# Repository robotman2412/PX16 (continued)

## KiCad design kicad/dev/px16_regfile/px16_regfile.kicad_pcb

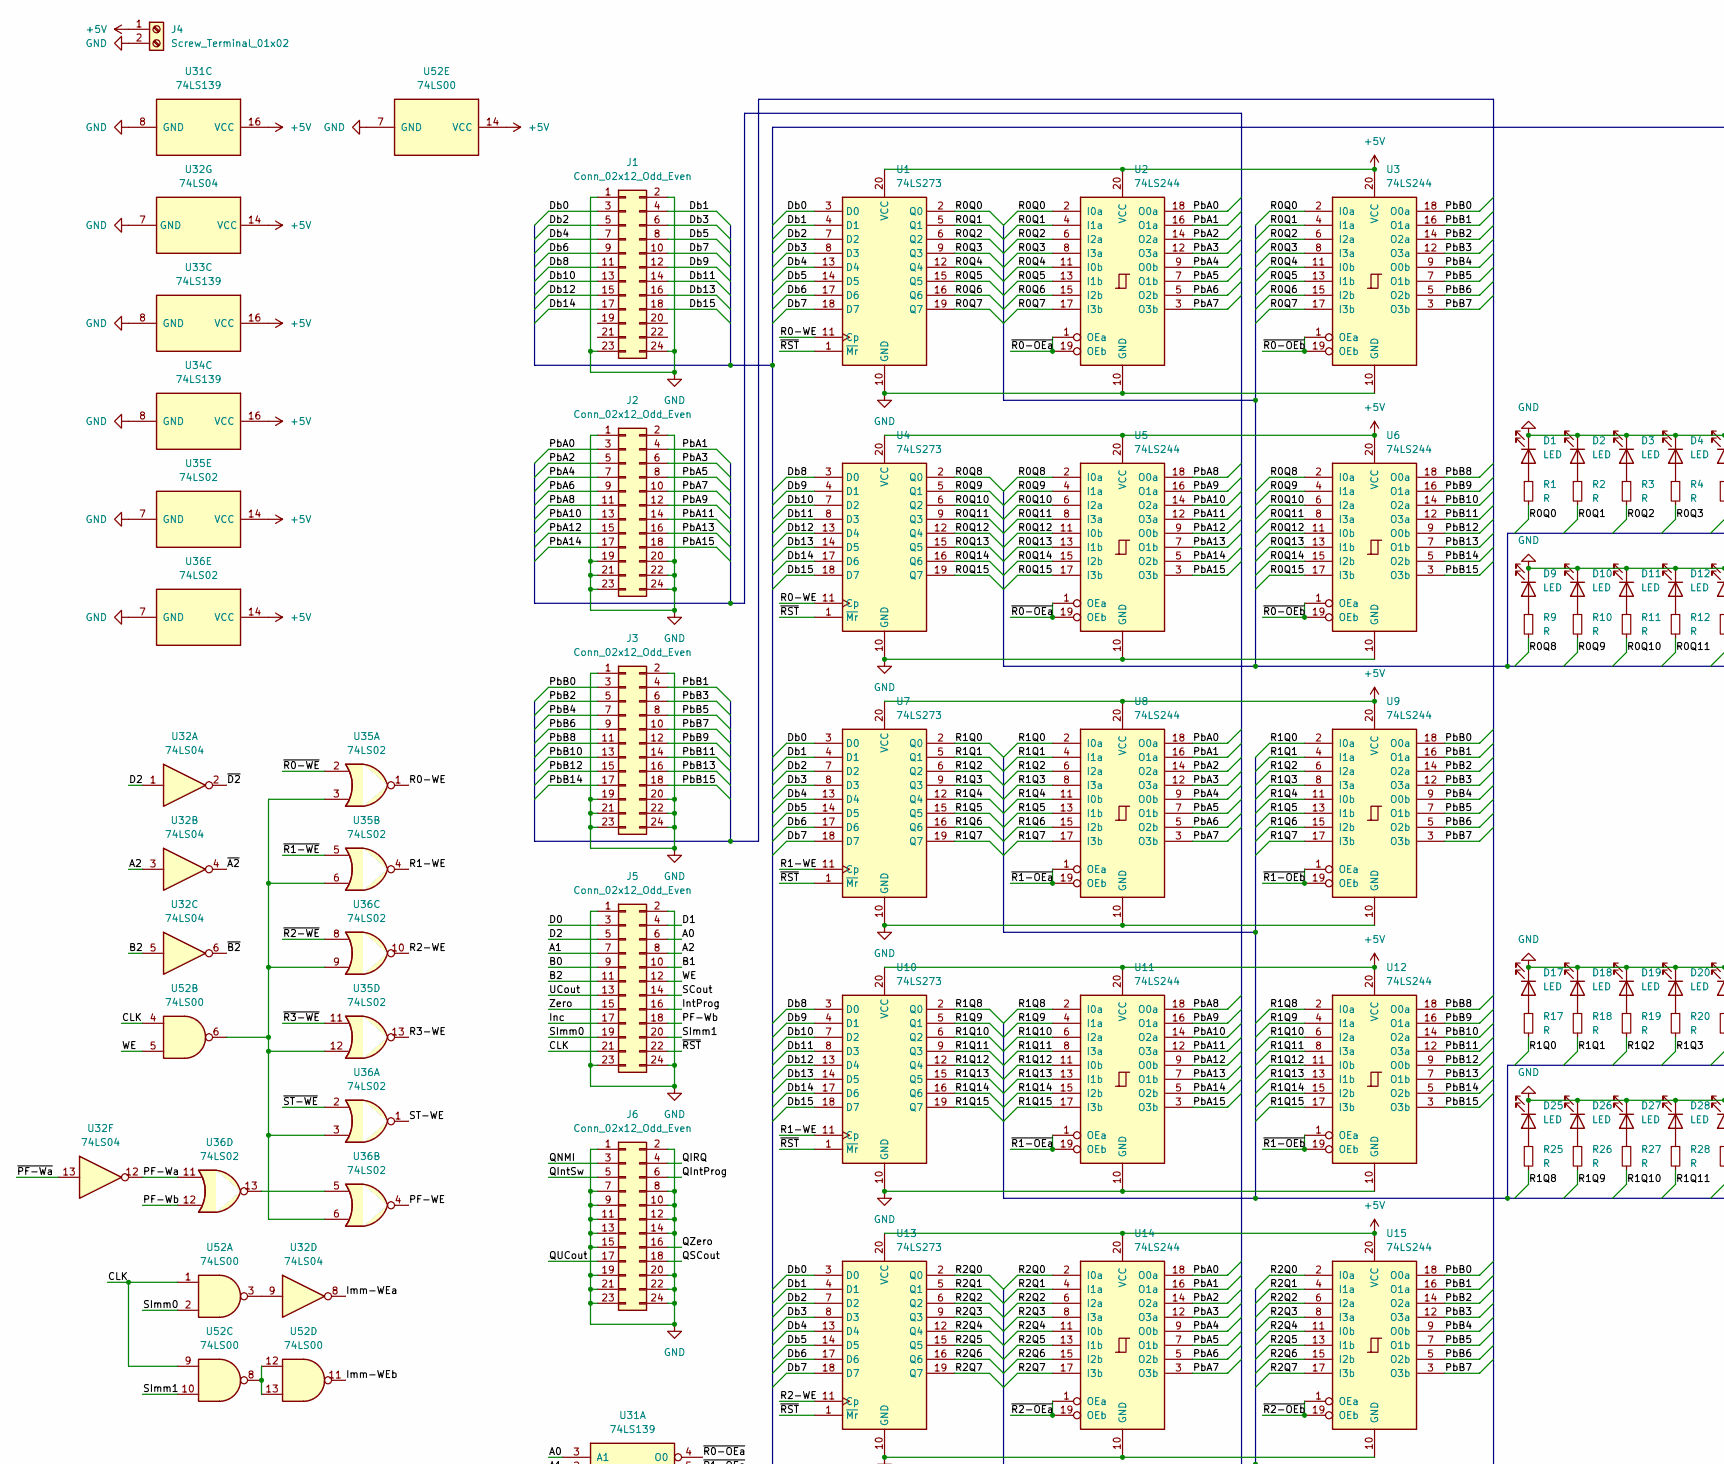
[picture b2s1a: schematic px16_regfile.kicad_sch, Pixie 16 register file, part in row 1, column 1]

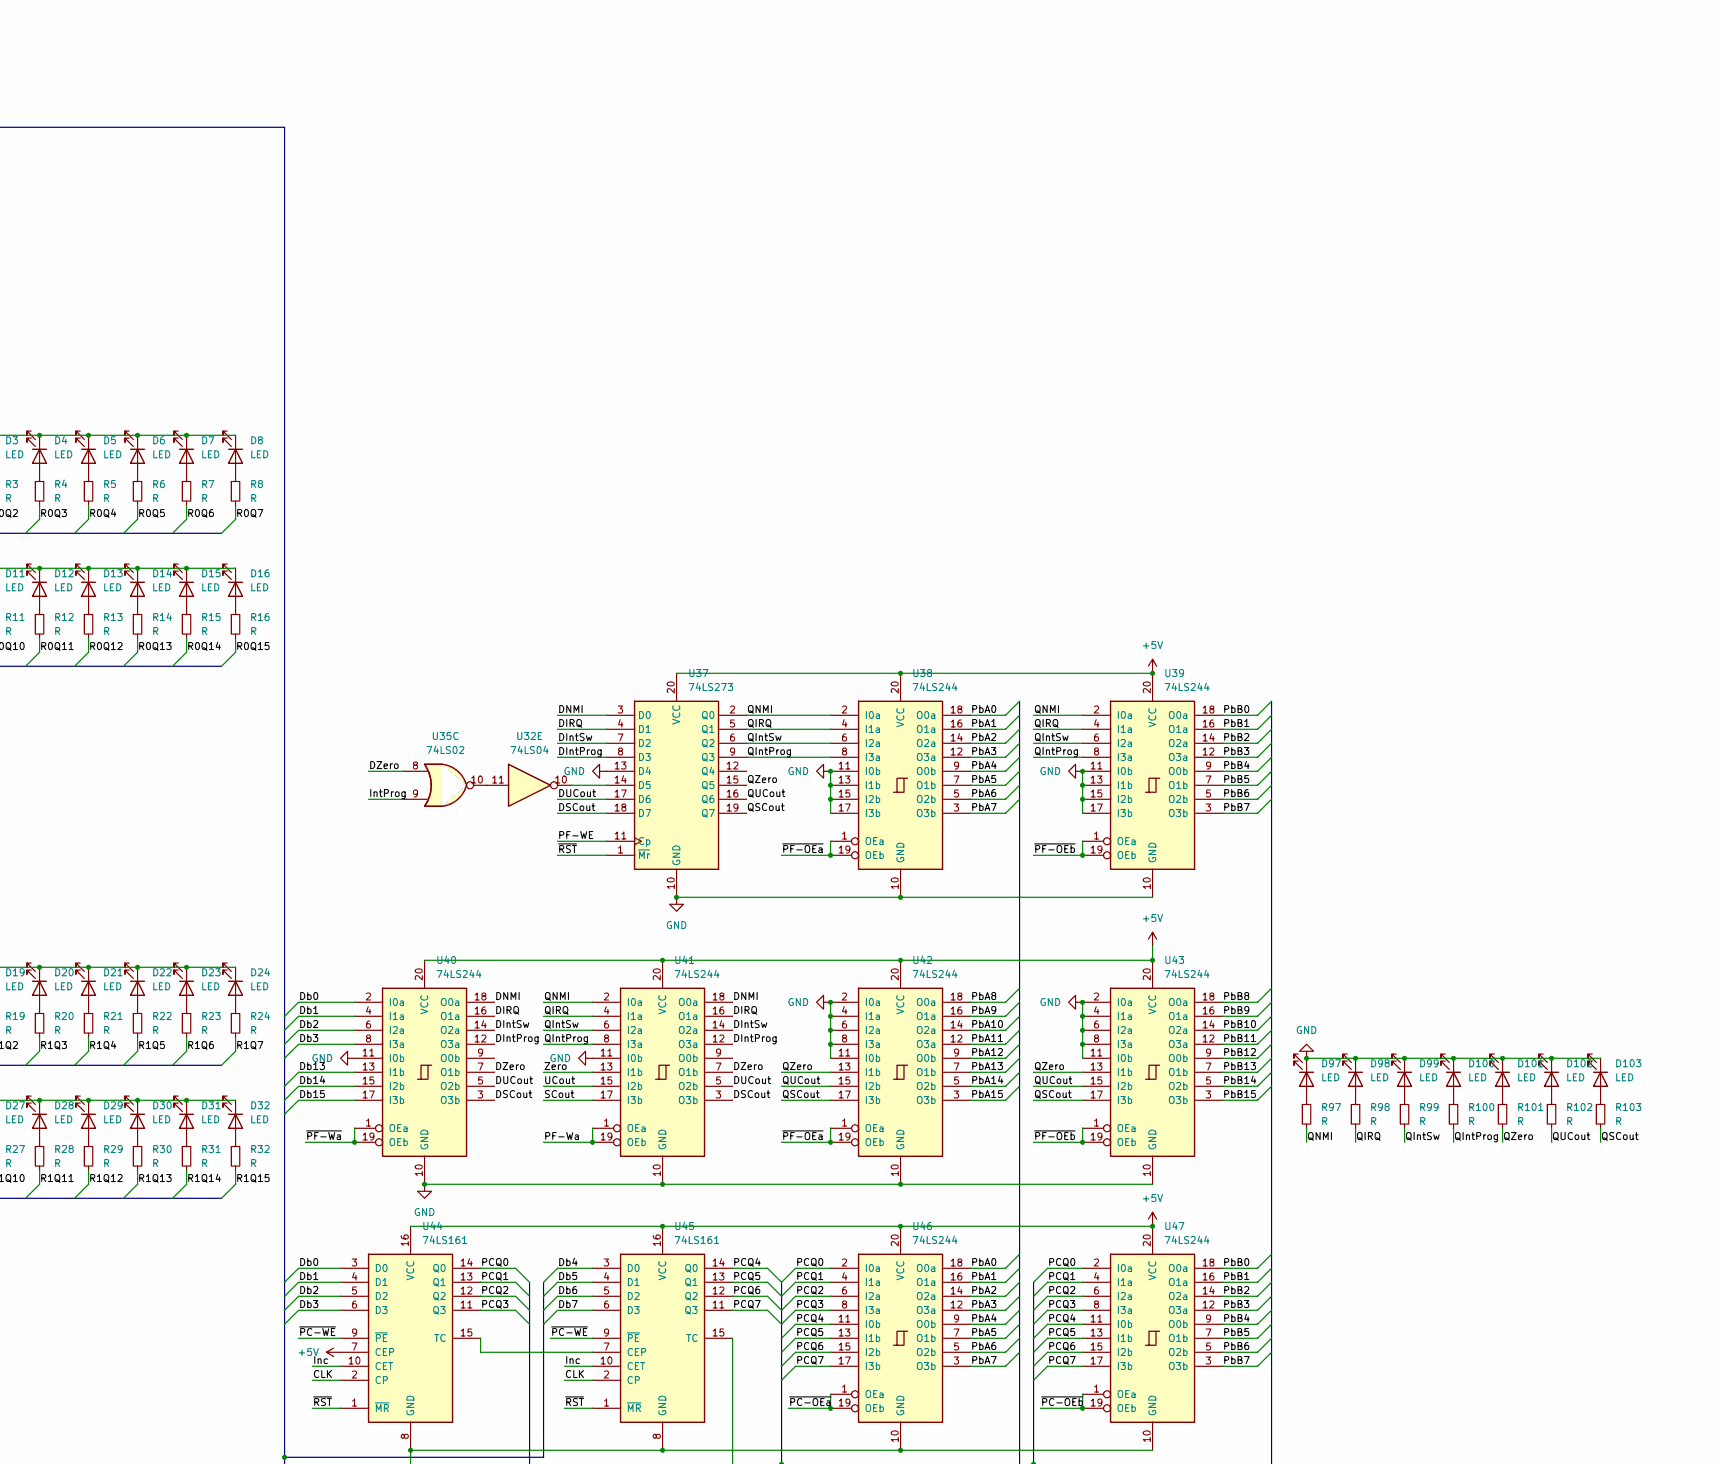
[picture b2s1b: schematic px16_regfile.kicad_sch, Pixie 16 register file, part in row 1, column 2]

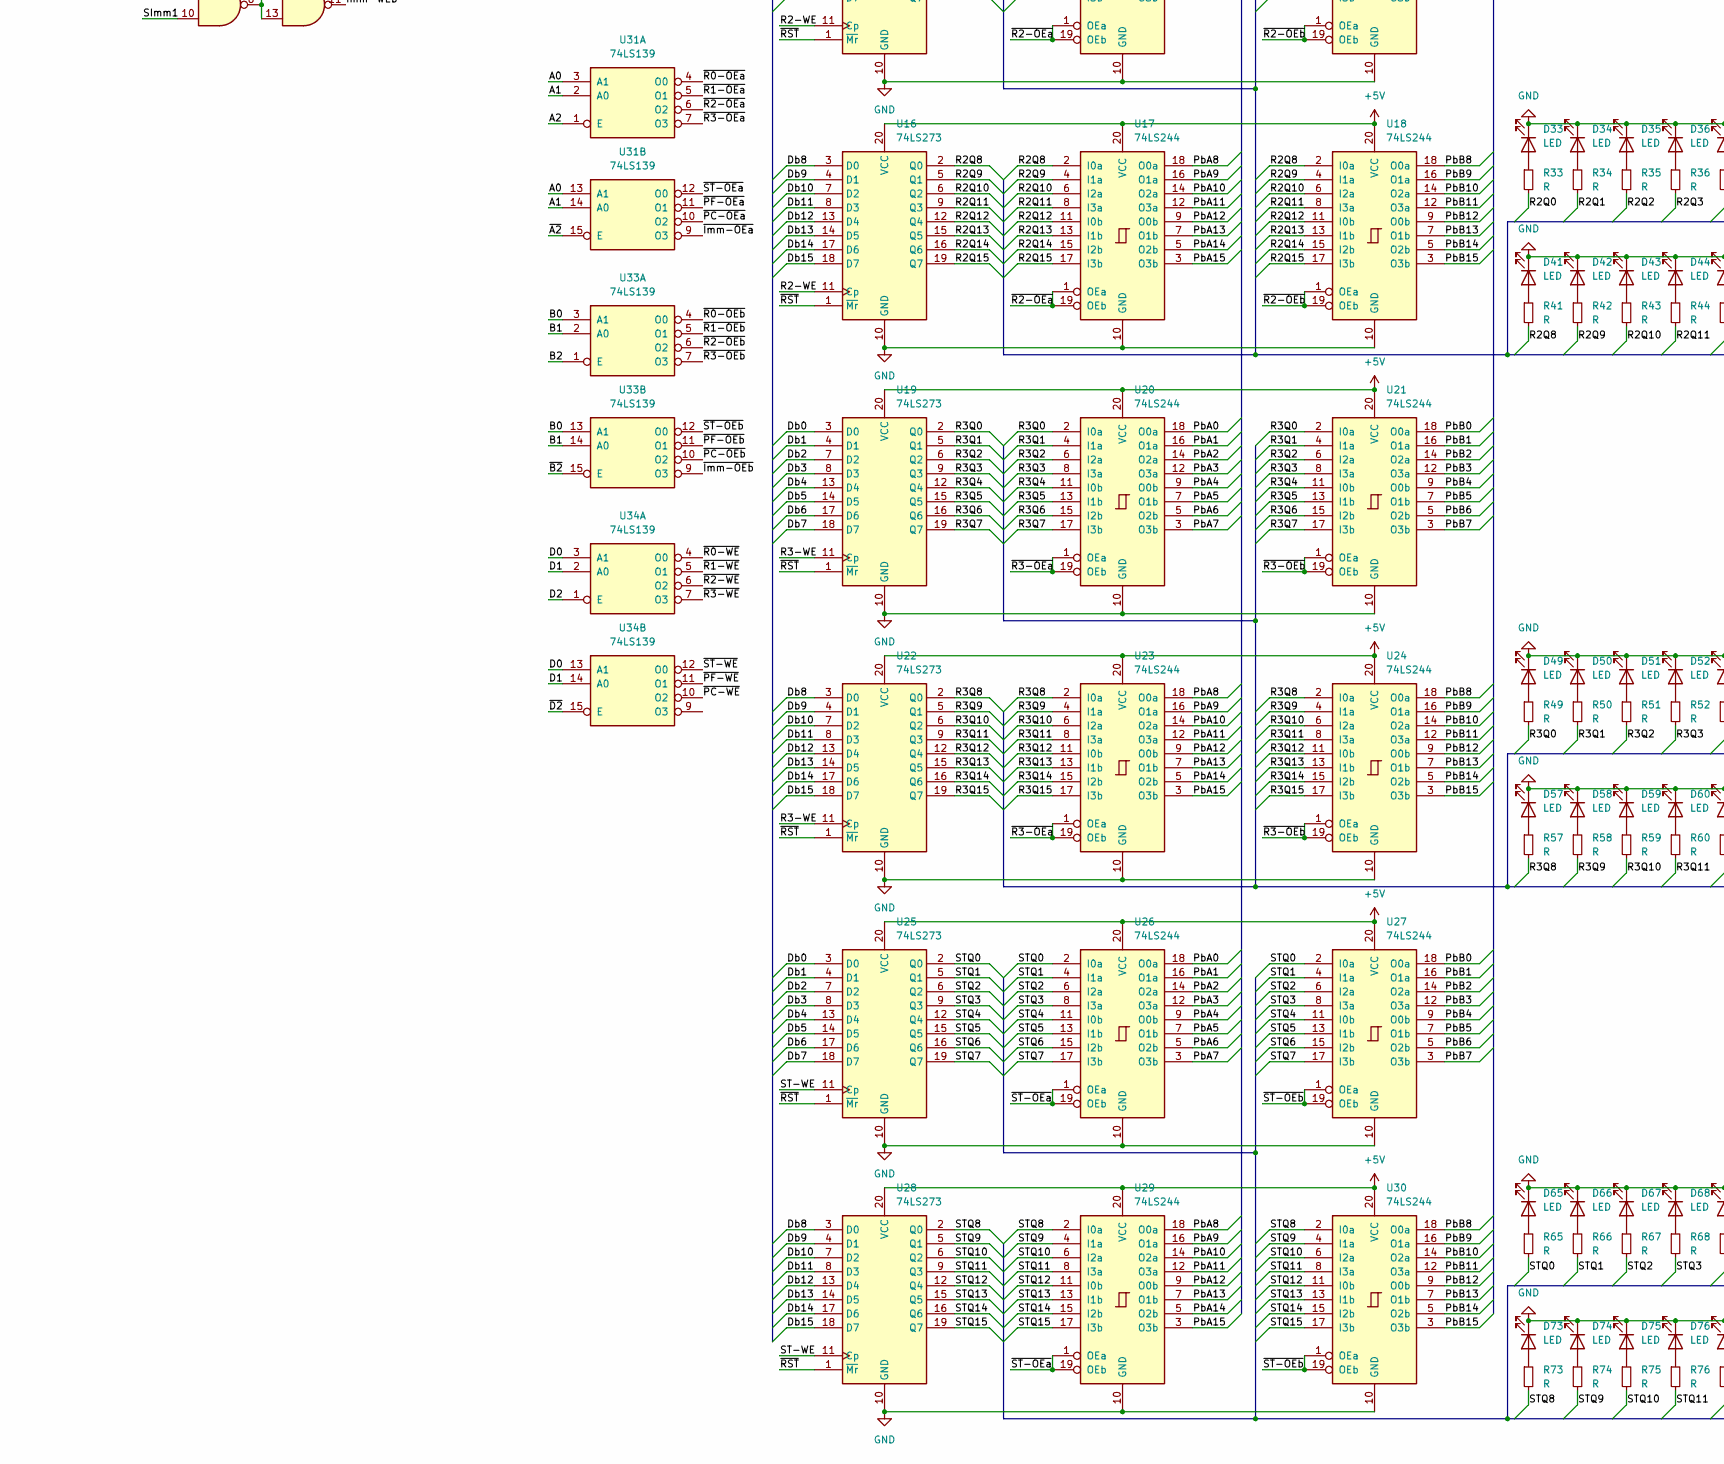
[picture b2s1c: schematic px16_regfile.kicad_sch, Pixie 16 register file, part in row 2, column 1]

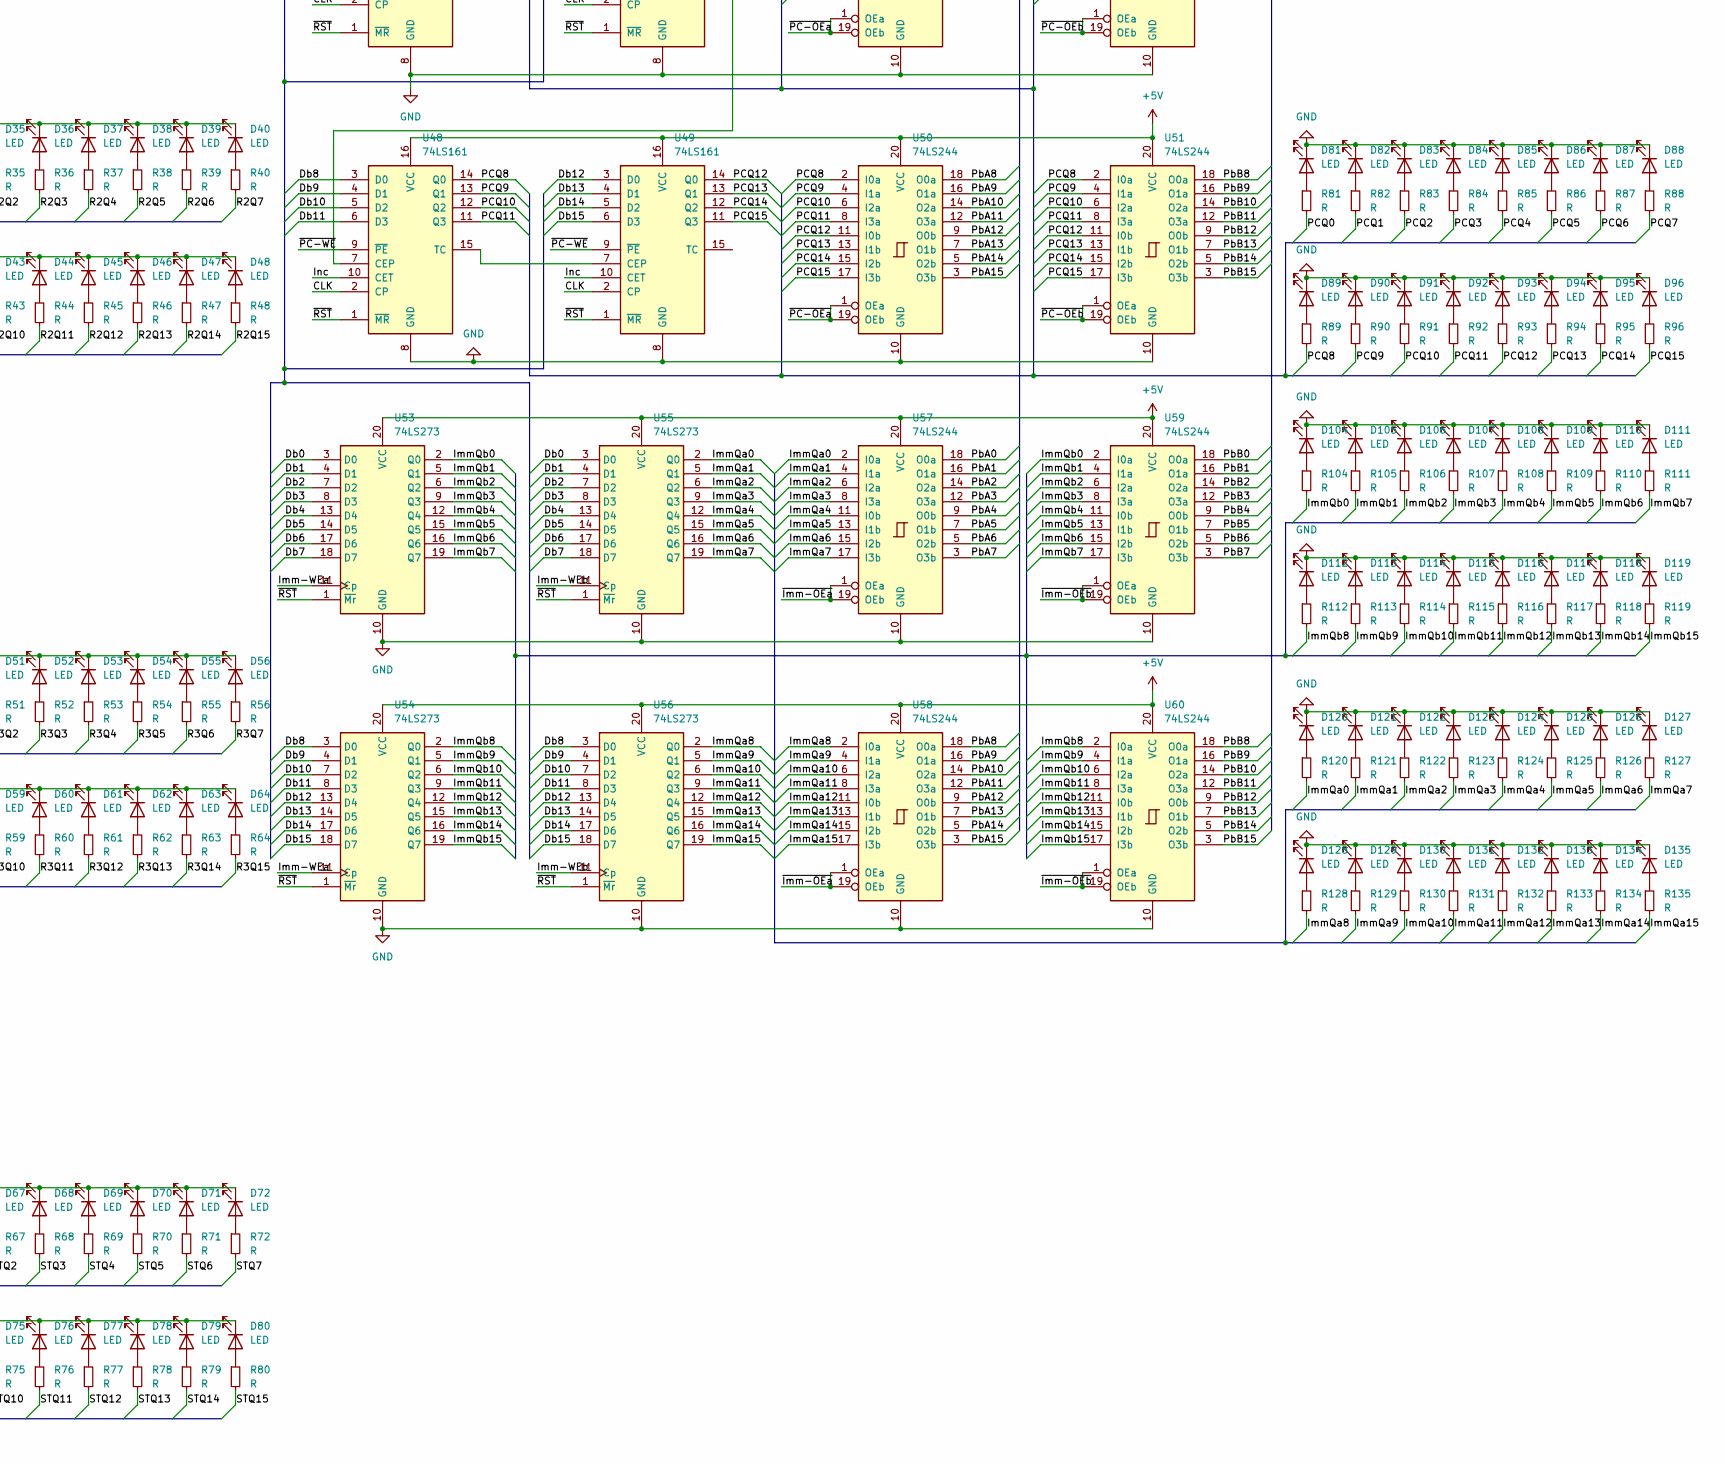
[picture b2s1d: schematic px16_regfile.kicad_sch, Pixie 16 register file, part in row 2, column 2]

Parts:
D1, D2, D3, D4, D5, D6, D7, D8, D9, D10, D11, D12, D13, D14, D15, D16, D17, D18, D19, D20, D21, D22, D23, D24, D25, D26, D27, D28, D29, D30, D31, D32, D33, D34, D35, D36, D37, D38, D39, D40, D41, D42, D43, D44, D45, D46, D47, D48, D49, D50, D51, D52, D53, D54, D55, D56, D57, D58, D59, D60, D61, D62, D63, D64, D65, D66, D67, D68, D69, D70, D71, D72, D73, D74, D75, D76, D77, D78, D79, D80, D81, D82, D83, D84, D85, D86, D87, D88, D89, D90, D91, D92, D93, D94, D95, D96, D97, D98, D99, D100, D101, D102, D103, D104, D105, D106, D107, D108, D109, D110, D111, D112, D113, D114, D115, D116, D117, D118, D119, D120, D121, D122, D123, D124, D125, D126, D127, D128, D129, D130, D131, D132, D133, D134, D135: LED; LED_D5.0mm
J1, J2, J3, J5, J6: Conn_02x12_Odd_Even; PinHeader_2x12_P2.54mm_Vertical
J4: Screw_Terminal_01x02; TerminalBlock_bornier-2_P5.08mm
R1, R2, R3, R4, R5, R6, R7, R8, R9, R10, R11, R12, R13, R14, R15, R16, R17, R18, R19, R20, R21, R22, R23, R24, R25, R26, R27, R28, R29, R30, R31, R32, R33, R34, R35, R36, R37, R38, R39, R40, R41, R42, R43, R44, R45, R46, R47, R48, R49, R50, R51, R52, R53, R54, R55, R56, R57, R58, R59, R60, R61, R62, R63, R64, R65, R66, R67, R68, R69, R70, R71, R72, R73, R74, R75, R76, R77, R78, R79, R80, R81, R82, R83, R84, R85, R86, R87, R88, R89, R90, R91, R92, R93, R94, R95, R96, R97, R98, R99, R100, R101, R102, R103, R104, R105, R106, R107, R108, R109, R110, R111, R112, R113, R114, R115, R116, R117, R118, R119, R120, R121, R122, R123, R124, R125, R126, R127, R128, R129, R130, R131, R132, R133, R134, R135: R; R_Axial_DIN0207_L6.3mm_D2.5mm_P2.54mm_Vertical
U1, U4, U7, U10, U13, U16, U19, U22, U25, U28, U37, U53, U54, U55, U56: 74LS273; DIP-20_W7.62mm
U2, U3, U5, U6, U8, U9, U11, U12, U14, U15, U17, U18, U20, U21, U23, U24, U26, U27, U29, U30, U38, U39, U40, U41, U42, U43, U46, U47, U50, U51, U57, U58, U59, U60: 74LS244; DIP-20_W7.62mm
U31, U33, U34: 74LS139; DIP-16_W7.62mm
U32: 74LS04; DIP-14_W7.62mm
U35, U36: 74LS02; DIP-14_W7.62mm
U44, U45, U48, U49: 74LS161; DIP-16_W7.62mm
U52: 74LS00; DIP-14_W7.62mm

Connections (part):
+5V: J4.1, U1.20 (VCC), U2.20 (VCC), U3.20 (VCC), U4.20 (VCC), U5.20 (VCC), U6.20 (VCC), U7.20 (VCC), U8.20 (VCC), U9.20 (VCC), U10.20 (VCC), U11.20 (VCC), U12.20 (VCC), U13.20 (VCC), U14.20 (VCC), U15.20 (VCC), U16.20 (VCC), U17.20 (VCC), U18.20 (VCC), U19.20 (VCC), U20.20 (VCC), U21.20 (VCC), U22.20 (VCC), U23.20 (VCC), U24.20 (VCC), U25.20 (VCC), U26.20 (VCC), U27.20 (VCC), U28.20 (VCC), U29.20 (VCC), U30.20 (VCC), U31.16 (VCC), U32.14 (VCC), U33.16 (VCC), U34.16 (VCC), U35.14 (VCC), U36.14 (VCC), U37.20 (VCC), U38.20 (VCC), U39.20 (VCC), U40.20 (VCC), U41.20 (VCC), U42.20 (VCC), U43.20 (VCC), U44.7 (CEP), U44.16 (VCC), U45.16 (VCC), U46.20 (VCC), U47.20 (VCC), U48.16 (VCC), U49.16 (VCC), U50.20 (VCC), U51.20 (VCC), U52.14 (VCC), U53.20 (VCC), U54.20 (VCC), U55.20 (VCC), U56.20 (VCC), U57.20 (VCC), U58.20 (VCC), U59.20 (VCC), U60.20 (VCC)
/A0: J5.6, U31.3 (A1), U31.13 (A1)
/A1: J5.7, U31.2 (A0), U31.14 (A0)
/A2: J5.8, U31.1 (E), U32.3
/B0: J5.9, U33.3 (A1), U33.13 (A1)
/B1: J5.10, U33.2 (A0), U33.14 (A0)
/B2: J5.11, U32.5, U33.1 (E)
/CLK: J5.21, U44.2 (CP), U45.2 (CP), U48.2 (CP), U49.2 (CP), U52.1, U52.4, U52.9
/D0: J5.3, U34.3 (A1), U34.13 (A1)
/D1: J5.4, U34.2 (A0), U34.14 (A0)
/D2: J5.5, U32.1, U34.1 (E)
/DIRQ: U37.4 (D1), U40.16 (O1a), U41.16 (O1a)
/DIntProg: U37.8 (D3), U40.12 (O3a), U41.12 (O3a)
/DIntSw: U37.7 (D2), U40.14 (O2a), U41.14 (O2a)
/DNMI: U37.3 (D0), U40.18 (O0a), U41.18 (O0a)
/DSCout: U37.18 (D7), U40.3 (O3b), U41.3 (O3b)
/DUCout: U37.17 (D6), U40.5 (O2b), U41.5 (O2b)
/DZero: U35.8, U40.7 (O1b), U41.7 (O1b)
/Db0: J1.3, U1.3 (D0), U7.3 (D0), U13.3 (D0), U19.3 (D0), U25.3 (D0), U40.2 (I0a), U44.3 (D0), U53.3 (D0), U55.3 (D0)
/Db1: J1.4, U1.4 (D1), U7.4 (D1), U13.4 (D1), U19.4 (D1), U25.4 (D1), U40.4 (I1a), U44.4 (D1), U53.4 (D1), U55.4 (D1)
/Db2: J1.5, U1.7 (D2), U7.7 (D2), U13.7 (D2), U19.7 (D2), U25.7 (D2), U40.6 (I2a), U44.5 (D2), U53.7 (D2), U55.7 (D2)
/Db3: J1.6, U1.8 (D3), U7.8 (D3), U13.8 (D3), U19.8 (D3), U25.8 (D3), U40.8 (I3a), U44.6 (D3), U53.8 (D3), U55.8 (D3)
/Db4: J1.7, U1.13 (D4), U7.13 (D4), U13.13 (D4), U19.13 (D4), U25.13 (D4), U45.3 (D0), U53.13 (D4), U55.13 (D4)
/Db5: J1.8, U1.14 (D5), U7.14 (D5), U13.14 (D5), U19.14 (D5), U25.14 (D5), U45.4 (D1), U53.14 (D5), U55.14 (D5)
/Db6: J1.9, U1.17 (D6), U7.17 (D6), U13.17 (D6), U19.17 (D6), U25.17 (D6), U45.5 (D2), U53.17 (D6), U55.17 (D6)
/Db7: J1.10, U1.18 (D7), U7.18 (D7), U13.18 (D7), U19.18 (D7), U25.18 (D7), U45.6 (D3), U53.18 (D7), U55.18 (D7)
/Db8: J1.11, U4.3 (D0), U10.3 (D0), U16.3 (D0), U22.3 (D0), U28.3 (D0), U48.3 (D0), U54.3 (D0), U56.3 (D0)
/Db9: J1.12, U4.4 (D1), U10.4 (D1), U16.4 (D1), U22.4 (D1), U28.4 (D1), U48.4 (D1), U54.4 (D1), U56.4 (D1)
/Db10: J1.13, U4.7 (D2), U10.7 (D2), U16.7 (D2), U22.7 (D2), U28.7 (D2), U48.5 (D2), U54.7 (D2), U56.7 (D2)
/Db11: J1.14, U4.8 (D3), U10.8 (D3), U16.8 (D3), U22.8 (D3), U28.8 (D3), U48.6 (D3), U54.8 (D3), U56.8 (D3)
/Db12: J1.15, U4.13 (D4), U10.13 (D4), U16.13 (D4), U22.13 (D4), U28.13 (D4), U49.3 (D0), U54.13 (D4), U56.13 (D4)
/Db13: J1.16, U4.14 (D5), U10.14 (D5), U16.14 (D5), U22.14 (D5), U28.14 (D5), U40.13 (I1b), U49.4 (D1), U54.14 (D5), U56.14 (D5)
/Db14: J1.17, U4.17 (D6), U10.17 (D6), U16.17 (D6), U22.17 (D6), U28.17 (D6), U40.15 (I2b), U49.5 (D2), U54.17 (D6), U56.17 (D6)
/Db15: J1.18, U4.18 (D7), U10.18 (D7), U16.18 (D7), U22.18 (D7), U28.18 (D7), U40.17 (I3b), U49.6 (D3), U54.18 (D7), U56.18 (D7)
/Imm-WEa: U32.8, U53.11 (Cp), U54.11 (Cp)
/Imm-WEb: U52.11, U55.11 (Cp), U56.11 (Cp)
/ImmQa0: R120.2, U55.2 (Q0), U57.2 (I0a)
/ImmQa1: R121.2, U55.5 (Q1), U57.4 (I1a)
/ImmQa2: R122.2, U55.6 (Q2), U57.6 (I2a)
/ImmQa3: R123.2, U55.9 (Q3), U57.8 (I3a)
/ImmQa4: R124.2, U55.12 (Q4), U57.11 (I0b)
/ImmQa5: R125.2, U55.15 (Q5), U57.13 (I1b)
/ImmQa6: R126.2, U55.16 (Q6), U57.15 (I2b)
/ImmQa7: R127.2, U55.19 (Q7), U57.17 (I3b)
/ImmQa8: R128.2, U56.2 (Q0), U58.2 (I0a)
/ImmQa9: R129.2, U56.5 (Q1), U58.4 (I1a)
/ImmQa10: R130.2, U56.6 (Q2), U58.6 (I2a)
/ImmQa11: R131.2, U56.9 (Q3), U58.8 (I3a)
/ImmQa12: R132.2, U56.12 (Q4), U58.11 (I0b)
/ImmQa13: R133.2, U56.15 (Q5), U58.13 (I1b)
/ImmQa14: R134.2, U56.16 (Q6), U58.15 (I2b)
/ImmQa15: R135.2, U56.19 (Q7), U58.17 (I3b)
/ImmQb0: R104.2, U53.2 (Q0), U59.2 (I0a)
/ImmQb1: R105.2, U53.5 (Q1), U59.4 (I1a)
/ImmQb2: R106.2, U53.6 (Q2), U59.6 (I2a)
/ImmQb3: R107.2, U53.9 (Q3), U59.8 (I3a)
/ImmQb4: R108.2, U53.12 (Q4), U59.11 (I0b)
/ImmQb5: R109.2, U53.15 (Q5), U59.13 (I1b)
/ImmQb6: R110.2, U53.16 (Q6), U59.15 (I2b)
/ImmQb7: R111.2, U53.19 (Q7), U59.17 (I3b)
/ImmQb8: R112.2, U54.2 (Q0), U60.2 (I0a)
/ImmQb9: R113.2, U54.5 (Q1), U60.4 (I1a)
/ImmQb10: R114.2, U54.6 (Q2), U60.6 (I2a)
/ImmQb11: R115.2, U54.9 (Q3), U60.8 (I3a)
/ImmQb12: R116.2, U54.12 (Q4), U60.11 (I0b)
/ImmQb13: R117.2, U54.15 (Q5), U60.13 (I1b)
/ImmQb14: R118.2, U54.16 (Q6), U60.15 (I2b)
/ImmQb15: R119.2, U54.19 (Q7), U60.17 (I3b)
/Inc: J5.17, U44.10 (CET), U45.10 (CET), U48.10 (CET), U49.10 (CET)
/IntProg: J5.16, U35.9
/PCQ0: R81.2, U44.14 (Q0), U46.2 (I0a), U47.2 (I0a)
/PCQ1: R82.2, U44.13 (Q1), U46.4 (I1a), U47.4 (I1a)
/PCQ2: R83.2, U44.12 (Q2), U46.6 (I2a), U47.6 (I2a)
/PCQ3: R84.2, U44.11 (Q3), U46.8 (I3a), U47.8 (I3a)
/PCQ4: R85.2, U45.14 (Q0), U46.11 (I0b), U47.11 (I0b)
/PCQ5: R86.2, U45.13 (Q1), U46.13 (I1b), U47.13 (I1b)
/PCQ6: R87.2, U45.12 (Q2), U46.15 (I2b), U47.15 (I2b)
/PCQ7: R88.2, U45.11 (Q3), U46.17 (I3b), U47.17 (I3b)
/PCQ8: R89.2, U48.14 (Q0), U50.2 (I0a), U51.2 (I0a)
/PCQ9: R90.2, U48.13 (Q1), U50.4 (I1a), U51.4 (I1a)
/PCQ10: R91.2, U48.12 (Q2), U50.6 (I2a), U51.6 (I2a)
/PCQ11: R92.2, U48.11 (Q3), U50.8 (I3a), U51.8 (I3a)
/PCQ12: R93.2, U49.14 (Q0), U50.11 (I0b), U51.11 (I0b)
/PCQ13: R94.2, U49.13 (Q1), U50.13 (I1b), U51.13 (I1b)
/PCQ14: R95.2, U49.12 (Q2), U50.15 (I2b), U51.15 (I2b)
/PCQ15: R96.2, U49.11 (Q3), U50.17 (I3b), U51.17 (I3b)
/PF-WE: U36.4, U37.11 (Cp)
/PF-Wa: U32.12, U36.11, U41.1 (OEa), U41.19 (OEb)
/PF-Wb: J5.18, U36.12
/PbA0: J2.3, U2.18 (O0a), U8.18 (O0a), U14.18 (O0a), U20.18 (O0a), U26.18 (O0a), U38.18 (O0a), U46.18 (O0a), U57.18 (O0a)
/PbA1: J2.4, U2.16 (O1a), U8.16 (O1a), U14.16 (O1a), U20.16 (O1a), U26.16 (O1a), U38.16 (O1a), U46.16 (O1a), U57.16 (O1a)
/PbA2: J2.5, U2.14 (O2a), U8.14 (O2a), U14.14 (O2a), U20.14 (O2a), U26.14 (O2a), U38.14 (O2a), U46.14 (O2a), U57.14 (O2a)
/PbA3: J2.6, U2.12 (O3a), U8.12 (O3a), U14.12 (O3a), U20.12 (O3a), U26.12 (O3a), U38.12 (O3a), U46.12 (O3a), U57.12 (O3a)
/PbA4: J2.7, U2.9 (O0b), U8.9 (O0b), U14.9 (O0b), U20.9 (O0b), U26.9 (O0b), U38.9 (O0b), U46.9 (O0b), U57.9 (O0b)
/PbA5: J2.8, U2.7 (O1b), U8.7 (O1b), U14.7 (O1b), U20.7 (O1b), U26.7 (O1b), U38.7 (O1b), U46.7 (O1b), U57.7 (O1b)
/PbA6: J2.9, U2.5 (O2b), U8.5 (O2b), U14.5 (O2b), U20.5 (O2b), U26.5 (O2b), U38.5 (O2b), U46.5 (O2b), U57.5 (O2b)
/PbA7: J2.10, U2.3 (O3b), U8.3 (O3b), U14.3 (O3b), U20.3 (O3b), U26.3 (O3b), U38.3 (O3b), U46.3 (O3b), U57.3 (O3b)
/PbA8: J2.11, U5.18 (O0a), U11.18 (O0a), U17.18 (O0a), U23.18 (O0a), U29.18 (O0a), U42.18 (O0a), U50.18 (O0a), U58.18 (O0a)
/PbA9: J2.12, U5.16 (O1a), U11.16 (O1a), U17.16 (O1a), U23.16 (O1a), U29.16 (O1a), U42.16 (O1a), U50.16 (O1a), U58.16 (O1a)
/PbA10: J2.13, U5.14 (O2a), U11.14 (O2a), U17.14 (O2a), U23.14 (O2a), U29.14 (O2a), U42.14 (O2a), U50.14 (O2a), U58.14 (O2a)
/PbA11: J2.14, U5.12 (O3a), U11.12 (O3a), U17.12 (O3a), U23.12 (O3a), U29.12 (O3a), U42.12 (O3a), U50.12 (O3a), U58.12 (O3a)
/PbA12: J2.15, U5.9 (O0b), U11.9 (O0b), U17.9 (O0b), U23.9 (O0b), U29.9 (O0b), U42.9 (O0b), U50.9 (O0b), U58.9 (O0b)
/PbA13: J2.16, U5.7 (O1b), U11.7 (O1b), U17.7 (O1b), U23.7 (O1b), U29.7 (O1b), U42.7 (O1b), U50.7 (O1b), U58.7 (O1b)
/PbA14: J2.17, U5.5 (O2b), U11.5 (O2b), U17.5 (O2b), U23.5 (O2b), U29.5 (O2b), U42.5 (O2b), U50.5 (O2b), U58.5 (O2b)
/PbA15: J2.18, U5.3 (O3b), U11.3 (O3b), U17.3 (O3b), U23.3 (O3b), U29.3 (O3b), U42.3 (O3b), U50.3 (O3b), U58.3 (O3b)
/PbB0: J3.3, U3.18 (O0a), U9.18 (O0a), U15.18 (O0a), U21.18 (O0a), U27.18 (O0a), U39.18 (O0a), U47.18 (O0a), U59.18 (O0a)
/PbB1: J3.4, U3.16 (O1a), U9.16 (O1a), U15.16 (O1a), U21.16 (O1a), U27.16 (O1a), U39.16 (O1a), U47.16 (O1a), U59.16 (O1a)
/PbB2: J3.5, U3.14 (O2a), U9.14 (O2a), U15.14 (O2a), U21.14 (O2a), U27.14 (O2a), U39.14 (O2a), U47.14 (O2a), U59.14 (O2a)
/PbB3: J3.6, U3.12 (O3a), U9.12 (O3a), U15.12 (O3a), U21.12 (O3a), U27.12 (O3a), U39.12 (O3a), U47.12 (O3a), U59.12 (O3a)
/PbB4: J3.7, U3.9 (O0b), U9.9 (O0b), U15.9 (O0b), U21.9 (O0b), U27.9 (O0b), U39.9 (O0b), U47.9 (O0b), U59.9 (O0b)
/PbB5: J3.8, U3.7 (O1b), U9.7 (O1b), U15.7 (O1b), U21.7 (O1b), U27.7 (O1b), U39.7 (O1b), U47.7 (O1b), U59.7 (O1b)
/PbB6: J3.9, U3.5 (O2b), U9.5 (O2b), U15.5 (O2b), U21.5 (O2b), U27.5 (O2b), U39.5 (O2b), U47.5 (O2b), U59.5 (O2b)
/PbB7: J3.10, U3.3 (O3b), U9.3 (O3b), U15.3 (O3b), U21.3 (O3b), U27.3 (O3b), U39.3 (O3b), U47.3 (O3b), U59.3 (O3b)
/PbB8: J3.11, U6.18 (O0a), U12.18 (O0a), U18.18 (O0a), U24.18 (O0a), U30.18 (O0a), U43.18 (O0a), U51.18 (O0a), U60.18 (O0a)
/PbB9: J3.12, U6.16 (O1a), U12.16 (O1a), U18.16 (O1a), U24.16 (O1a), U30.16 (O1a), U43.16 (O1a), U51.16 (O1a), U60.16 (O1a)
/PbB10: J3.13, U6.14 (O2a), U12.14 (O2a), U18.14 (O2a), U24.14 (O2a), U30.14 (O2a), U43.14 (O2a), U51.14 (O2a), U60.14 (O2a)
/PbB11: J3.14, U6.12 (O3a), U12.12 (O3a), U18.12 (O3a), U24.12 (O3a), U30.12 (O3a), U43.12 (O3a), U51.12 (O3a), U60.12 (O3a)
/PbB12: J3.15, U6.9 (O0b), U12.9 (O0b), U18.9 (O0b), U24.9 (O0b), U30.9 (O0b), U43.9 (O0b), U51.9 (O0b), U60.9 (O0b)
/PbB13: J3.16, U6.7 (O1b), U12.7 (O1b), U18.7 (O1b), U24.7 (O1b), U30.7 (O1b), U43.7 (O1b), U51.7 (O1b), U60.7 (O1b)
/PbB14: J3.17, U6.5 (O2b), U12.5 (O2b), U18.5 (O2b), U24.5 (O2b), U30.5 (O2b), U43.5 (O2b), U51.5 (O2b), U60.5 (O2b)
/PbB15: J3.18, U6.3 (O3b), U12.3 (O3b), U18.3 (O3b), U24.3 (O3b), U30.3 (O3b), U43.3 (O3b), U51.3 (O3b), U60.3 (O3b)
/QIRQ: J6.4, R98.2, U37.5 (Q1), U38.4 (I1a), U39.4 (I1a), U41.4 (I1a)
/QIntProg: J6.6, R100.2, U37.9 (Q3), U38.8 (I3a), U39.8 (I3a), U41.8 (I3a)
/QIntSw: J6.5, R99.2, U37.6 (Q2), U38.6 (I2a), U39.6 (I2a), U41.6 (I2a)
/QNMI: J6.3, R97.2, U37.2 (Q0), U38.2 (I0a), U39.2 (I0a), U41.2 (I0a)
/QSCout: J6.18, R103.2, U37.19 (Q7), U42.17 (I3b), U43.17 (I3b)
/QUCout: J6.17, R102.2, U37.16 (Q6), U42.15 (I2b), U43.15 (I2b)
/QZero: J6.16, R101.2, U37.15 (Q5), U42.13 (I1b), U43.13 (I1b)
/R0-WE: U1.11 (Cp), U4.11 (Cp), U35.1
/R0Q0: R1.2, U1.2 (Q0), U2.2 (I0a), U3.2 (I0a)
/R0Q1: R2.2, U1.5 (Q1), U2.4 (I1a), U3.4 (I1a)
/R0Q2: R3.2, U1.6 (Q2), U2.6 (I2a), U3.6 (I2a)
/R0Q3: R4.2, U1.9 (Q3), U2.8 (I3a), U3.8 (I3a)
/R0Q4: R5.2, U1.12 (Q4), U2.11 (I0b), U3.11 (I0b)
/R0Q5: R6.2, U1.15 (Q5), U2.13 (I1b), U3.13 (I1b)
/R0Q6: R7.2, U1.16 (Q6), U2.15 (I2b), U3.15 (I2b)
/R0Q7: R8.2, U1.19 (Q7), U2.17 (I3b), U3.17 (I3b)
/R0Q8: R9.2, U4.2 (Q0), U5.2 (I0a), U6.2 (I0a)
/R0Q9: R10.2, U4.5 (Q1), U5.4 (I1a), U6.4 (I1a)
/R0Q10: R11.2, U4.6 (Q2), U5.6 (I2a), U6.6 (I2a)
/R0Q11: R12.2, U4.9 (Q3), U5.8 (I3a), U6.8 (I3a)
/R0Q12: R13.2, U4.12 (Q4), U5.11 (I0b), U6.11 (I0b)
/R0Q13: R14.2, U4.15 (Q5), U5.13 (I1b), U6.13 (I1b)
/R0Q14: R15.2, U4.16 (Q6), U5.15 (I2b), U6.15 (I2b)
/R0Q15: R16.2, U4.19 (Q7), U5.17 (I3b), U6.17 (I3b)
/R1-WE: U7.11 (Cp), U10.11 (Cp), U35.4
/R1Q0: R17.2, U7.2 (Q0), U8.2 (I0a), U9.2 (I0a)
/R1Q1: R18.2, U7.5 (Q1), U8.4 (I1a), U9.4 (I1a)
/R1Q2: R19.2, U7.6 (Q2), U8.6 (I2a), U9.6 (I2a)
/R1Q3: R20.2, U7.9 (Q3), U8.8 (I3a), U9.8 (I3a)
/R1Q4: R21.2, U7.12 (Q4), U8.11 (I0b), U9.11 (I0b)
/R1Q5: R22.2, U7.15 (Q5), U8.13 (I1b), U9.13 (I1b)
/R1Q6: R23.2, U7.16 (Q6), U8.15 (I2b), U9.15 (I2b)
/R1Q7: R24.2, U7.19 (Q7), U8.17 (I3b), U9.17 (I3b)
/R1Q8: R25.2, U10.2 (Q0), U11.2 (I0a), U12.2 (I0a)
/R1Q9: R26.2, U10.5 (Q1), U11.4 (I1a), U12.4 (I1a)
/R1Q10: R27.2, U10.6 (Q2), U11.6 (I2a), U12.6 (I2a)
/R1Q11: R28.2, U10.9 (Q3), U11.8 (I3a), U12.8 (I3a)
/R1Q12: R29.2, U10.12 (Q4), U11.11 (I0b), U12.11 (I0b)
/R1Q13: R30.2, U10.15 (Q5), U11.13 (I1b), U12.13 (I1b)
/R1Q14: R31.2, U10.16 (Q6), U11.15 (I2b), U12.15 (I2b)
/R1Q15: R32.2, U10.19 (Q7), U11.17 (I3b), U12.17 (I3b)
/R2-WE: U13.11 (Cp), U16.11 (Cp), U36.10
/R2Q0: R33.2, U13.2 (Q0), U14.2 (I0a), U15.2 (I0a)
/R2Q1: R34.2, U13.5 (Q1), U14.4 (I1a), U15.4 (I1a)
/R2Q2: R35.2, U13.6 (Q2), U14.6 (I2a), U15.6 (I2a)
/R2Q3: R36.2, U13.9 (Q3), U14.8 (I3a), U15.8 (I3a)
/R2Q4: R37.2, U13.12 (Q4), U14.11 (I0b), U15.11 (I0b)
/R2Q5: R38.2, U13.15 (Q5), U14.13 (I1b), U15.13 (I1b)
/R2Q6: R39.2, U13.16 (Q6), U14.15 (I2b), U15.15 (I2b)
/R2Q7: R40.2, U13.19 (Q7), U14.17 (I3b), U15.17 (I3b)
/R2Q8: R41.2, U16.2 (Q0), U17.2 (I0a), U18.2 (I0a)
/R2Q9: R42.2, U16.5 (Q1), U17.4 (I1a), U18.4 (I1a)
/R2Q10: R43.2, U16.6 (Q2), U17.6 (I2a), U18.6 (I2a)
/R2Q11: R44.2, U16.9 (Q3), U17.8 (I3a), U18.8 (I3a)
/R2Q12: R45.2, U16.12 (Q4), U17.11 (I0b), U18.11 (I0b)
/R2Q13: R46.2, U16.15 (Q5), U17.13 (I1b), U18.13 (I1b)
/R2Q14: R47.2, U16.16 (Q6), U17.15 (I2b), U18.15 (I2b)
/R2Q15: R48.2, U16.19 (Q7), U17.17 (I3b), U18.17 (I3b)
/R3-WE: U19.11 (Cp), U22.11 (Cp), U35.13
/R3Q0: R49.2, U19.2 (Q0), U20.2 (I0a), U21.2 (I0a)
/R3Q1: R50.2, U19.5 (Q1), U20.4 (I1a), U21.4 (I1a)
/R3Q2: R51.2, U19.6 (Q2), U20.6 (I2a), U21.6 (I2a)
/R3Q3: R52.2, U19.9 (Q3), U20.8 (I3a), U21.8 (I3a)
/R3Q4: R53.2, U19.12 (Q4), U20.11 (I0b), U21.11 (I0b)
/R3Q5: R54.2, U19.15 (Q5), U20.13 (I1b), U21.13 (I1b)
/R3Q6: R55.2, U19.16 (Q6), U20.15 (I2b), U21.15 (I2b)
/R3Q7: R56.2, U19.19 (Q7), U20.17 (I3b), U21.17 (I3b)
/R3Q8: R57.2, U22.2 (Q0), U23.2 (I0a), U24.2 (I0a)
/R3Q9: R58.2, U22.5 (Q1), U23.4 (I1a), U24.4 (I1a)
/R3Q10: R59.2, U22.6 (Q2), U23.6 (I2a), U24.6 (I2a)
/R3Q11: R60.2, U22.9 (Q3), U23.8 (I3a), U24.8 (I3a)
/R3Q12: R61.2, U22.12 (Q4), U23.11 (I0b), U24.11 (I0b)
/R3Q13: R62.2, U22.15 (Q5), U23.13 (I1b), U24.13 (I1b)
/R3Q14: R63.2, U22.16 (Q6), U23.15 (I2b), U24.15 (I2b)
/R3Q15: R64.2, U22.19 (Q7), U23.17 (I3b), U24.17 (I3b)
/SCout: J5.14, U41.17 (I3b)
/SImm0: J5.19, U52.2
/SImm1: J5.20, U52.10
/ST-WE: U25.11 (Cp), U28.11 (Cp), U36.1
/STQ0: R65.2, U25.2 (Q0), U26.2 (I0a), U27.2 (I0a)
/STQ1: R66.2, U25.5 (Q1), U26.4 (I1a), U27.4 (I1a)
/STQ2: R67.2, U25.6 (Q2), U26.6 (I2a), U27.6 (I2a)
/STQ3: R68.2, U25.9 (Q3), U26.8 (I3a), U27.8 (I3a)
/STQ4: R69.2, U25.12 (Q4), U26.11 (I0b), U27.11 (I0b)
/STQ5: R70.2, U25.15 (Q5), U26.13 (I1b), U27.13 (I1b)
/STQ6: R71.2, U25.16 (Q6), U26.15 (I2b), U27.15 (I2b)
/STQ7: R72.2, U25.19 (Q7), U26.17 (I3b), U27.17 (I3b)
/STQ8: R73.2, U28.2 (Q0), U29.2 (I0a), U30.2 (I0a)
/STQ9: R74.2, U28.5 (Q1), U29.4 (I1a), U30.4 (I1a)
/STQ10: R75.2, U28.6 (Q2), U29.6 (I2a), U30.6 (I2a)
/STQ11: R76.2, U28.9 (Q3), U29.8 (I3a), U30.8 (I3a)
/STQ12: R77.2, U28.12 (Q4), U29.11 (I0b), U30.11 (I0b)
/STQ13: R78.2, U28.15 (Q5), U29.13 (I1b), U30.13 (I1b)
/STQ14: R79.2, U28.16 (Q6), U29.15 (I2b), U30.15 (I2b)
/STQ15: R80.2, U28.19 (Q7), U29.17 (I3b), U30.17 (I3b)
/UCout: J5.13, U41.15 (I2b)
/WE: J5.12, U52.5
/Zero: J5.15, U41.13 (I1b)
/~A2: U31.15 (E), U32.4
/~B2: U32.6, U33.15 (E)
/~D2: U32.2, U34.15 (E)
/~Imm-OEa: U31.9 (O3), U57.1 (OEa), U57.19 (OEb), U58.1 (OEa), U58.19 (OEb)
/~Imm-OEb: U33.9 (O3), U59.1 (OEa), U59.19 (OEb), U60.1 (OEa), U60.19 (OEb)
/~PC-OEa: U31.10 (O2), U46.1 (OEa), U46.19 (OEb), U50.1 (OEa), U50.19 (OEb)
/~PC-OEb: U33.10 (O2), U47.1 (OEa), U47.19 (OEb), U51.1 (OEa), U51.19 (OEb)
/~PC-WE: U34.10 (O2), U44.9 (~PE), U45.9 (~PE), U48.9 (~PE), U49.9 (~PE)
/~PF-OEa: U31.11 (O1), U38.1 (OEa), U38.19 (OEb), U42.1 (OEa), U42.19 (OEb)
/~PF-OEb: U33.11 (O1), U39.1 (OEa), U39.19 (OEb), U43.1 (OEa), U43.19 (OEb)
/~PF-WE: U34.11 (O1)
/~PF-Wa: U32.13, U40.1 (OEa), U40.19 (OEb)
/~R0-OEa: U2.1 (OEa), U2.19 (OEb), U5.1 (OEa), U5.19 (OEb), U31.4 (O0)
/~R0-OEb: U3.1 (OEa), U3.19 (OEb), U6.1 (OEa), U6.19 (OEb), U33.4 (O0)
/~R0-WE: U34.4 (O0), U35.2
/~R1-OEa: U8.1 (OEa), U8.19 (OEb), U11.1 (OEa), U11.19 (OEb), U31.5 (O1)
/~R1-OEb: U9.1 (OEa), U9.19 (OEb), U12.1 (OEa), U12.19 (OEb), U33.5 (O1)
/~R1-WE: U34.5 (O1), U35.5
/~R2-OEa: U14.1 (OEa), U14.19 (OEb), U17.1 (OEa), U17.19 (OEb), U31.6 (O2)
/~R2-OEb: U15.1 (OEa), U15.19 (OEb), U18.1 (OEa), U18.19 (OEb), U33.6 (O2)
/~R2-WE: U34.6 (O2), U36.8
/~R3-OEa: U20.1 (OEa), U20.19 (OEb), U23.1 (OEa), U23.19 (OEb), U31.7 (O3)
/~R3-OEb: U21.1 (OEa), U21.19 (OEb), U24.1 (OEa), U24.19 (OEb), U33.7 (O3)
/~R3-WE: U34.7 (O3), U35.11
/~RST: J5.22, U1.1 (~Mr), U4.1 (~Mr), U7.1 (~Mr), U10.1 (~Mr), U13.1 (~Mr), U16.1 (~Mr), U19.1 (~Mr), U22.1 (~Mr), U25.1 (~Mr), U28.1 (~Mr), U37.1 (~Mr), U44.1 (~MR), U45.1 (~MR), U48.1 (~MR), U49.1 (~MR), U53.1 (~Mr), U54.1 (~Mr), U55.1 (~Mr), U56.1 (~Mr)
/~ST-OEa: U26.1 (OEa), U26.19 (OEb), U29.1 (OEa), U29.19 (OEb), U31.12 (O0)
/~ST-OEb: U27.1 (OEa), U27.19 (OEb), U30.1 (OEa), U30.19 (OEb), U33.12 (O0)
/~ST-WE: U34.12 (O0), U36.2
GND: D1.1 (K), D2.1 (K), D3.1 (K), D4.1 (K), D5.1 (K), D6.1 (K), D7.1 (K), D8.1 (K), D9.1 (K), D10.1 (K), D11.1 (K), D12.1 (K), D13.1 (K), D14.1 (K), D15.1 (K), D16.1 (K), D17.1 (K), D18.1 (K), D19.1 (K), D20.1 (K), D21.1 (K), D22.1 (K), D23.1 (K), D24.1 (K), D25.1 (K), D26.1 (K), D27.1 (K), D28.1 (K), D29.1 (K), D30.1 (K), D31.1 (K), D32.1 (K), D33.1 (K), D34.1 (K), D35.1 (K), D36.1 (K), D37.1 (K), D38.1 (K), D39.1 (K), D40.1 (K), D41.1 (K), D42.1 (K), D43.1 (K), D44.1 (K), D45.1 (K), D46.1 (K), D47.1 (K), D48.1 (K), D49.1 (K), D50.1 (K), D51.1 (K), D52.1 (K), D53.1 (K), D54.1 (K), D55.1 (K), D56.1 (K), D57.1 (K), D58.1 (K), D59.1 (K), D60.1 (K), D61.1 (K), D62.1 (K), D63.1 (K), D64.1 (K), D65.1 (K), D66.1 (K), D67.1 (K), D68.1 (K), D69.1 (K), D70.1 (K), D71.1 (K), D72.1 (K), D73.1 (K), D74.1 (K), D75.1 (K), D76.1 (K), D77.1 (K), D78.1 (K), D79.1 (K), D80.1 (K)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
unnamed: D1.2 (A), R1.1
unnamed: D2.2 (A), R2.1
unnamed: D3.2 (A), R3.1
unnamed: D4.2 (A), R4.1
unnamed: D5.2 (A), R5.1
unnamed: D6.2 (A), R6.1
unnamed: D7.2 (A), R7.1
unnamed: D8.2 (A), R8.1
unnamed: D9.2 (A), R9.1
unnamed: D10.2 (A), R10.1
unnamed: D11.2 (A), R11.1
unnamed: D12.2 (A), R12.1
unnamed: D13.2 (A), R13.1
unnamed: D14.2 (A), R14.1
unnamed: D15.2 (A), R15.1
unnamed: D16.2 (A), R16.1
unnamed: D17.2 (A), R17.1
unnamed: D18.2 (A), R18.1
unnamed: D19.2 (A), R19.1
unnamed: D20.2 (A), R20.1
unnamed: D21.2 (A), R21.1
unnamed: D22.2 (A), R22.1
unnamed: D23.2 (A), R23.1
unnamed: D24.2 (A), R24.1
unnamed: D25.2 (A), R25.1
unnamed: D26.2 (A), R26.1
unnamed: D27.2 (A), R27.1
unnamed: D28.2 (A), R28.1
unnamed: D29.2 (A), R29.1
unnamed: D30.2 (A), R30.1
unnamed: D31.2 (A), R31.1
unnamed: D32.2 (A), R32.1
unnamed: D33.2 (A), R33.1
unnamed: D34.2 (A), R34.1
unnamed: D35.2 (A), R35.1
unnamed: D36.2 (A), R36.1
unnamed: D37.2 (A), R37.1
unnamed: D38.2 (A), R38.1
unnamed: D39.2 (A), R39.1
unnamed: D40.2 (A), R40.1
unnamed: D41.2 (A), R41.1
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
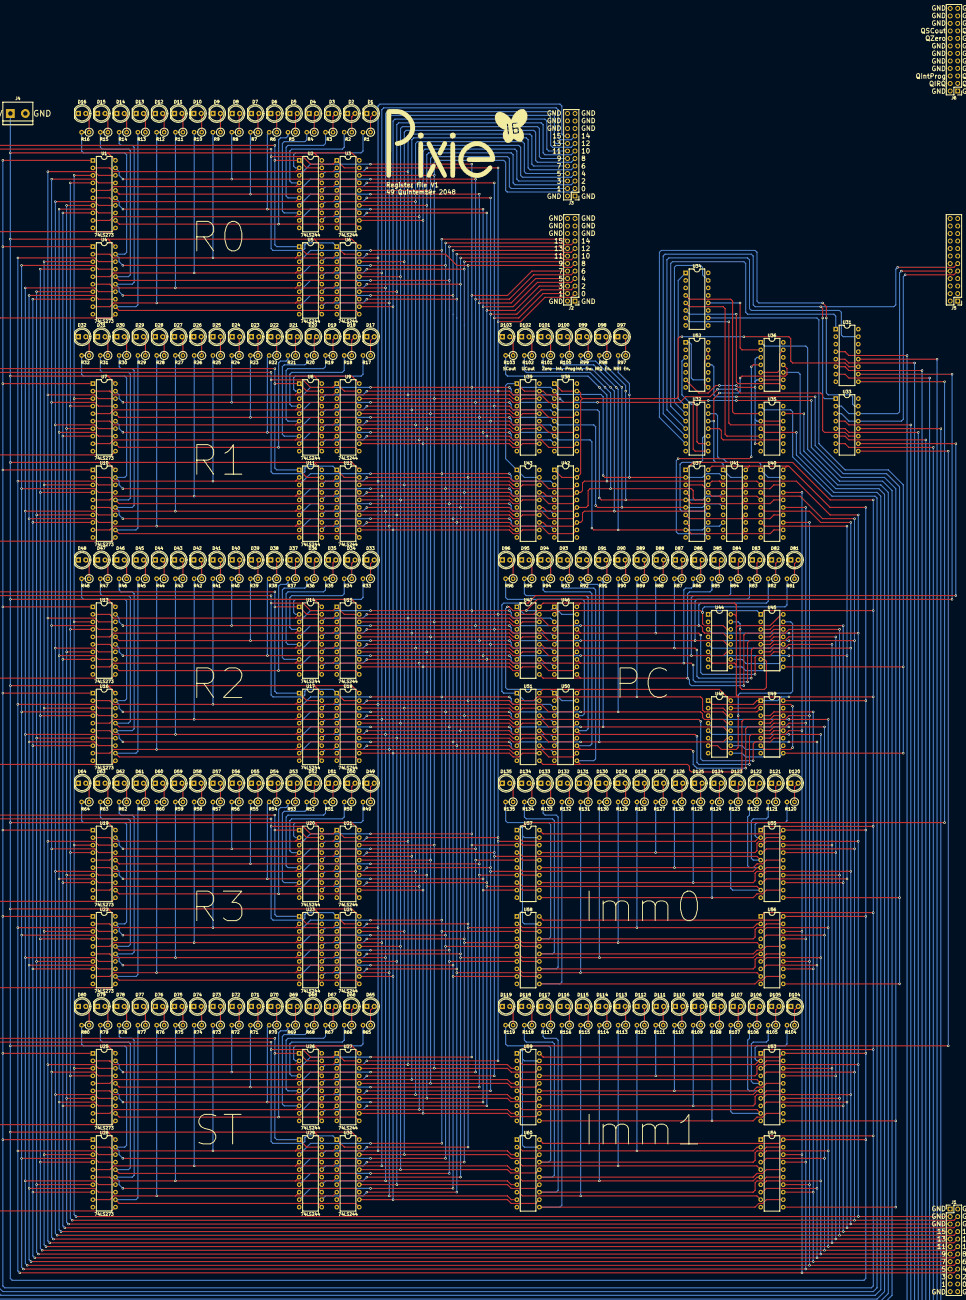
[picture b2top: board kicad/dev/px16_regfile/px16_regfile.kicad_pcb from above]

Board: 2 copper layers, 337 parts (0 on the bottom side), 391 nets.

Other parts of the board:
G1: LOGO
